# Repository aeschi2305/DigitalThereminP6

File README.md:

# DigitalTheremin
Project Files for the Bachelor Thesis digital Theremin

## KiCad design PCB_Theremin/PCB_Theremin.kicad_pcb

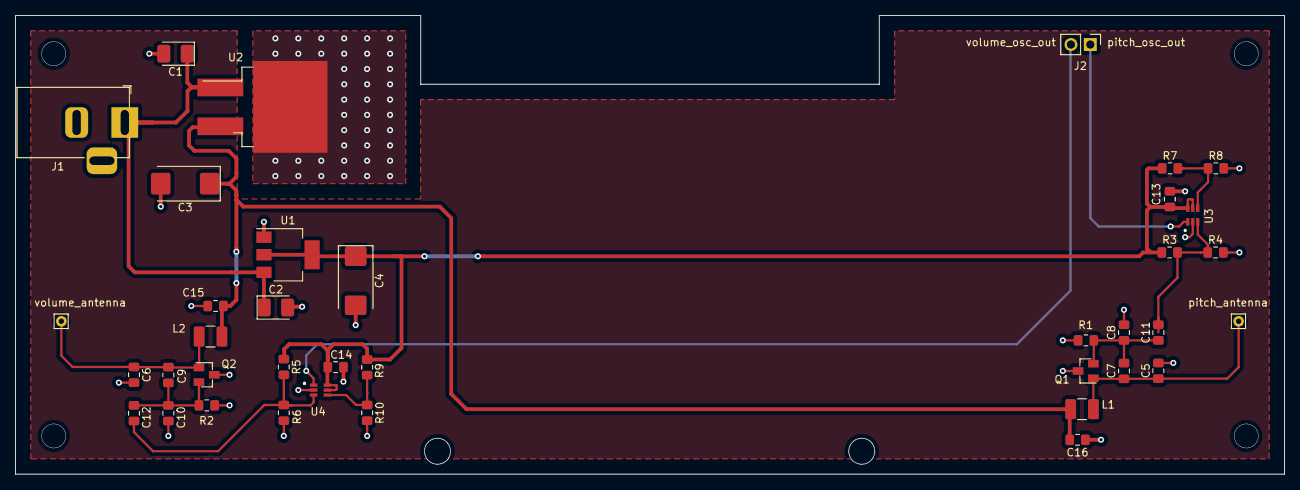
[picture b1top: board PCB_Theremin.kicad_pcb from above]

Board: 2 copper layers, 166.0 x 60.0 mm, 38 parts (0 on the bottom side), 14 nets.

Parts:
C1, C2: 10uF; CP_EIA-3528-21_Kemet-B
C3, C4: 100uF; CP_EIA-7343-43_Kemet-X_Pad2.25x2.55mm_HandSolder
C5, C6: 4.7p; C_0805_2012Metric_Pad1.15x1.40mm_HandSolder
C7, C9: 270p; C_0805_2012Metric_Pad1.15x1.40mm_HandSolder
C8, C10: 100p; C_0805_2012Metric_Pad1.15x1.40mm_HandSolder
C11, C12: 120p; C_0805_2012Metric_Pad1.15x1.40mm_HandSolder
C13, C14, C15, C16: 100n; C_0805_2012Metric_Pad1.15x1.40mm_HandSolder
J1: Barrel_Jack_MountingPin; BarrelJack_Horizontal
J2: Conn_01x02_Male; PinHeader_1x02_P2.54mm_Vertical
L1, L2: 1m; L_1210_3225Metric_Pad1.42x2.65mm_HandSolder
Q1, Q2: J113; SOT-23
R1, R2: 4.7k; R_0805_2012Metric_Pad1.15x1.40mm_HandSolder
R3, R4, R5, R6, R7, R8, R9, R10: 10k; R_0805_2012Metric_Pad1.15x1.40mm_HandSolder
U1: LT1117-3.3V; SOT-223-3_TabPin2
U2: MC7809CD2TG; TO-263-2
U3, U4: LTC6752-4; SC6
pitch_antenna: Conn_01x01_Male; Pin_D0.7mm_L6.5mm_W1.8mm_FlatFork
volume_antenna: Conn_01x01_Male; Pin_D0.7mm_L6.5mm_W1.8mm_FlatFork

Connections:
+3V3: C4.1, C13.1, C14.1, R3.1, R5.1, R7.1, R9.1, U1.2, U3.5, U3.6, U4.5, U4.6
+9VA: C3.1, C15.2, C16.2, L1.1, L2.1, U2.3
+12V: C1.1, C2.1, J1.1, U1.3, U2.1
GND: C1.2, C2.2, C3.2, C4.2, C5.2, C6.2, C8.2, C10.2, C13.2, C14.2, C15.1, C16.1, J1.2, Q1.3, Q2.3, R1.2, R2.2, R4.2, R6.2, R8.2, R10.2, U1.1, U2.2, U3.2, U4.2
unnamed: C9.2, C10.1, C12.1, Q2.2, R2.1
unnamed: C7.2, C8.1, C11.1, Q1.2, R1.1
unnamed: C11.2, R3.2, R4.1, U3.3
unnamed: C12.2, R5.2, R6.1, U4.3
unnamed: R7.2, R8.1, U3.4
unnamed: R9.2, R10.1, U4.4
pitch_antenna: C5.1, C7.1, L1.2, Q1.1, pitch_antenna.1
pitch_osc_out: J2.1, U3.1
volume_antenna: C6.1, C9.1, L2.2, Q2.1, volume_antenna.1
volume_osc_out: J2.2, U4.1

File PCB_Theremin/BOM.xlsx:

Reference | Value | Toleranz | Footprint | Manufacturer Part Number (MPN) | Supplier Part Number (SPN) mouser | Supplier Part Number (SPN) digi-Key
R1 | 4.7kOhm | 1% 0.25W | 0805 |  |  | 311-4.70KCRCT-ND
R2 | 4.7kOhm | 1% 0.25W | 0805 |  |  | 311-4.70KCRCT-ND
R3 | 10kOhm | 1% 0.25W | 0805 |  |  | RNCP0805FTD10K0TR-ND
R4 | 10kOhm | 1% 0.25W | 0805 |  |  | RNCP0805FTD10K0TR-ND
R5 | 10kOhm | 1% 0.25W | 0805 |  |  | RNCP0805FTD10K0TR-ND
R6 | 10kOhm | 1% 0.25W | 0805 |  |  | RNCP0805FTD10K0TR-ND
R7 | 10kOhm | 1% 0.25W | 0805 |  |  | RNCP0805FTD10K0TR-ND
R8 | 10kOhm | 1% 0.25W | 0805 |  |  | RNCP0805FTD10K0TR-ND
R9 | 10kOhm | 1% 0.25W | 0805 |  |  | RNCP0805FTD10K0TR-ND
R10 | 10kOhm | 1% 0.25W | 0805 |  |  | RNCP0805FTD10K0TR-ND
C1 | 10uF | 20% 35V | 3528 | TCJB106M035S0200 | 581-TCJB106M035S0200 | 478-8057-2-ND
C2 | 10uF | 20% 35V | 3528 | TCJB106M035S0200 | 581-TCJB106M035S0200 | 478-8057-2-ND
C3 | 100uF | 20% 25V | 7343 | TAJE107M025RNJV | 581-TAJE107M025RNJV | 478-10748-1-ND
C4 | 100uF | 20% 25V | 7343 | TAJE107M025RNJV | 581-TAJE107M025RNJV | 478-10748-1-ND
C5 | 4.7pF | 10% 25VDC | 0805 |  |  | 720-1721-1-ND
C6 | 4.7pF | 10% 25VDC | 0805 |  |  | 720-1721-1-ND
C7 | 270pF | 10% 25VDC | 0805 |  |  | 311-3749-2-ND
C8 | 100pF | 10% 25VDC | 0805 |  |  | 399-9150-2-ND
C9 | 270pF | 10% 25VDC | 0805 |  |  | 311-3749-2-ND
C10 | 100pF | 10% 25VDC | 0805 |  |  | 399-9150-2-ND
C11 | 120pF | 10% 25VDC | 0805 |  |  | 720-1705-1-ND
C12 | 120pF | 10% 25VDC | 0805 |  |  | 720-1705-1-ND
C13 | 100nF | 10% 25VDC | 0805 |  |  | 399-1177-1-ND
C14 | 100nF | 10% 25VDC | 0805 |  |  | 399-1177-1-ND
C15 | 100nF | 10% 25VDC | 0805 |  |  | 399-1177-1-ND
C16 | 100nF | 10% 25VDC | 0805 |  |  | 399-1177-1-ND
L1 | 1mH | 10% 75mA 16.9ohms | 1210 | CBC3225T102KRV | 963-CBC3225T102KRV | 587-6403-2-ND
L2 | 1mH | 10% 75mA 16.9ohms | 1210 | CBC3225T102KRV | 963-CBC3225T102KRV | 587-6403-2-ND
Q1 | J113 |  | SOT-23 | MMBFJ113 | 512-MMBFJ113 | MMBFJ113TR-ND
Q2 | J113 |  | SOT-23 | MMBFJ113 | 512-MMBFJ113 | MMBFJ113TR-ND
U1 | LT1117-3.3V |  | 3-LEAD PLASTIC SOT-223 | LT1117CST-3.3#PBF | 584-LT1117CST-3.3PBF | LT1117CST-3.3#PBF
U2 | Voltage Regulators |  | D2PAK | MC7809CD2TG | 863-MC7809CD2TG | MC7809CD2TGOS
U3 | Analog Comparators |  | 6-LEAD PLASTIC SC70 | LTC6752HSC6-4#TRMPBF | 584-C6752HSC6-4TMPF | LTC6752HSC6-4#TRMPBFTR-ND
U4 | Analog Comparators |  | 6-LEAD PLASTIC SC70 | LTC6752HSC6-4#TRMPBF | 584-C6752HSC6-4TMPF | LTC6752HSC6-4#TRMPBFTR-ND
J1 | DC Barrel Jack |  |  | PRT-10811 | 474-PRT-10811 | 2092-KLDX-0202-A-ND
J2 | Headers |  | 2.54 mm Pitch | 4-103327-3 | 571-4-103327-3 | A26547-ND
J3 | Headers |  | 2.54 mm Pitch | 4-103327-4 | 571-4-103327-4 | A26547-ND
J4 | Headers |  | 2.54 mm Pitch | 4-103327-5 | 571-4-103327-5 | A26547-ND
J5 | Headers |  | 2.54 mm Pitch | 4-103327-6 | 571-4-103327-6 | A26547-ND

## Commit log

2020-03-25 added first commit
2020-04-13 added NIOS implementation
2020-04-13 added VHDL code from P5
2020-04-24 add Nios System for LCD programming
2020-04-24 Tongenerierung
2020-04-29 added TestP5
2020-05-01 changed TestP5
2020-05-01 Revert "changed TestP5"
    This reverts commit 9f2595aabba825db93f9037e5b138188af926830.
2020-05-06 Finished TestP5
2020-05-14 24bit
2020-07-06 added Theremin working
2020-07-13 changed gitignore
2020-07-13 Software LCD touch
2020-07-13 added frequency measurement
2020-07-15 graphic user interface
2020-07-16 added Test_freq_meas
2020-07-20 added Calibration and Glissando Component
2020-07-20 Dummy Komponenten software & hardware
2020-07-22 added working calibration
2020-07-22 Codec Volume test
2020-07-23 Vol_dummy & pitch dummy work with new adresss
2020-07-23 added glissando effect
2020-07-24 added Calibration and Glissando Test
2020-07-24 Volume_generation Simulation Questa
2020-07-24 added physically working Calibration and Glissando
2020-07-27 Code einigermassen aufgeräumt
2020-07-29 added final quartus project and changes to CalGlis
2020-07-29 Ton Anzeige funktioniert
2020-07-30 vhdl naming changes
2020-07-30 changes to final quartus project
2020-08-01 VHDL & Software changes
2020-08-01 changes to calibration, freq measurement and Glissando
2020-08-02 fixed frequency measurement
2020-08-03 Change Volume
2020-08-03 changed gitignore to allow workspace
2020-08-03 added workspace
2020-08-04 added a changed volume generation and fixed calibration
2020-08-06 added filter change test (only one FIR in pitch generation) and volume generation in vhdl
2020-08-07 fixed pitch display
2020-08-10 changed Pitch Reference Frequency
2020-08-10 visual changes to gui
2020-08-10 added non volatile programming files
2020-08-14 cleand code
2020-08-22 cleanup of vhdl and quartus project
2020-08-23 Theremin case
2020-08-23 PCB Theremin
2020-08-23 Step Files
